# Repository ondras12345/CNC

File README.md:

# CNC
My CNC 1610 configuration and CNC-related notes

See also https://ondra.sluka.cz/projects/1610-cnc/

## Software
- [Grbl firmware](https://github.com/gnea/grbl) (1.1h)
- [Candle Grbl controller](https://github.com/denvi/Candle/) - no longer used
- [bCNC Grbl controller](https://github.com/vlachoudis/bCNC)

## Configuration
- [My Grbl configuration](./GRBL-config.md)
- [My Candle configuration](./Candle)

## Documentation
Links to some useful docs:
- http://linuxcnc.org/docs/html/gcode.html
- https://github.com/Denvi/Candle/wiki
- https://github.com/gnea/grbl/wiki/Grbl-v1.1-Configuration
- https://github.com/gnea/grbl/wiki/Grbl-v1.1-Interface
- https://github.com/gnea/grbl/wiki/Grbl-v1.1-Commands

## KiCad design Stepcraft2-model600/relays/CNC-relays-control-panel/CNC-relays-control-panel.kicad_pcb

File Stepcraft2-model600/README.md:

# Stepcraft2 model 600
This directory contains notes about my Stepcraft CNC machine and accessories:
- Stepcraft 2 - 600 desktop CNC-/3D-System
- HF500 spindle + Hailea ACO-208 air pump ([Stepcraft YouTube](https://www.youtube.com/watch?v=FoeF6cgP0wI))
- Enclosure for desktop CNC/3D systems Stepcraft 600
- UC100 CNC motion controller (currently unused)
- Stepcraft USB module for WinPC-NC (currently unused)
- Stepcraft drag knife
- Stepcraft 3D touch probe
- Stepcraft tool length sensor
- dust shoe

## Spindle
Warning: when controlled with the front panel rotary encoder and button,
the VFD ignores the state of all e-stop switches! As far as I can tell,
this is by design.

## Laser
I wanted to mount the 0.5 W diode laser that I got with my old 1610 CNC
machine in the Stepcraft 43 mm holder, so 3D printed an adapter part:
`laser-mounitng-adapter.FCStd`. The model is parametric, the OD parameter
should probably be increased a bit. See `Params` spreadsheet.
I have also published the model on printables:
https://www.printables.com/model/1005261-stepcraft-43-mm-holder-for-33-mm-laser

## LinuxCNC configuration
### Latency
I am running LinuxCNC with standard preempt_RT kernel on a HP Compaq
dc7700 small form factor (Pentium D). After tuning the BIOS settings
(usual LinuxCNC recommendations + permanently running fans at maximum
speeds), I still had 105 us of base thread latency in `latency-test`.

After settings `i915.enable_dc=0 isolcpus=1` on the linux kernel command
line, I now have 24.5 us worst case latency. (It is important to let
`latency-test` run for a long time, the maximum latency was 14 us
for the first 20 minutes in my case.)

### Stepper drivers
I found this useful webpage: https://www.weigu.lu/other_projects/cnc/grbling_stepcraft/index.html
Apparently, the stepper drivers are A5979.
Based on its datasheet, I set the timings in `stepconf` like this:

| parameter       | value   |
|:---------------:|:-------:|
| Step Time       | 1000 ns |
| Step Space      | 1000 ns |
| Direction Hold  | 200 ns  |
| Direction Setup | 200 ns  |

### Axis config
I got the CNC with a CD that contained a Mach4 configuration file. I used
that as a reference for setting up axes in `stepconf`.

See my [linuxcnc config](../linuxcnc/stepcraft2-model600/).

## Maintenance
- https://cncfaq.us/maintenance/

### 2024-10-26
- The belt situation has gotten worse since the last log, the machine would
  fail to move completely.
- Right (closer to the window) Y pulley was wrapped with steel wire from the
  belt.
- Right Y pulley was moving on the leadscrew - the grub screw was loose.
- Removed right Y pulley from leadscrew. There was grease on the interface,
  I wiped it clean and put the pulley back on.
- Replaced belt.
- Tutorials followed:
  - https://www.youtube.com/watch?v=cZNLv7w0tCs
  - https://www.youtube.com/watch?v=zrz58k_M_2g
  - https://www.youtube.com/watch?v=GKEKqlukmYs
  - https://www.youtube.com/watch?v=RyjEeQAENyk
- When the belt was too loose, it would skip during rapid moves.
- Now it stalls when crashed during rapid, but still skips at F100.
- Now the Y axis is really easy to stall.
- Fixed by tightening the belt a little more. Why does that help?!

### 2024-09-28
- Removed belt cover, it was covered with coarse black dust.
- The side of the belt closer to the work area is damaged and folds over
  easily. This cannot be fixed without replacing the belt.
- Ordered new belt:
  - https://eshop.profitek.cz/stepcraft-cnc-systemy/remen-pro-pohon-v-ose-y/
  - also available from https://shop.stepcraft-systems.com/Tooth-Belt-600

### 2024-09-25
Found issues:
- Right Y axis leadscrew has huge backlash.
- Y belt folds over during Y- jog.

### 2024-09-22
- X axis cable guide was assembled incorrectly by the previous owner, the
  smaller hose was put into the bigger hole in the feedthrough and the bigger
  hose does not fit. Designed a 3D printed part to prevent the wires from
  bending in this location: `X-cable-guide.FCStd`.

### 2024-08
- Cleaned and lubricated all axes.
- Disassembled Z axis (removed stepper) and adjusted roller tension properly.

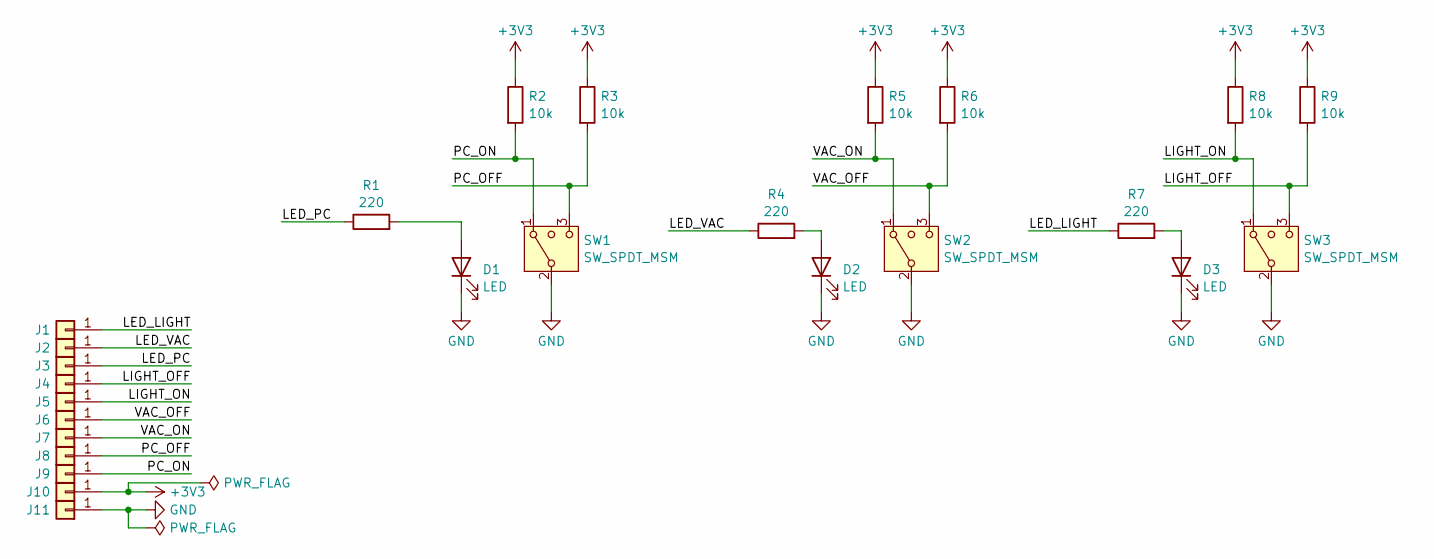
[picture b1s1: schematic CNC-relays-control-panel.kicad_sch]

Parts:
D1, D2, D3: LED; LED_1206_3216Metric_ReverseMount_Hole1.8x2.4mm
J1, J2, J3, J4, J6, J8, J10, J11: Conn_01x01; SolderWire-0.25sqmm_1x01_D0.65mm_OD2mm_Relief
J5, J7, J9: Conn_01x01; SolderWire-0.25sqmm_1x01_D0.65mm_OD2mm_Relief2x
R1, R4, R7: 220; R_1206_3216Metric_Pad1.30x1.75mm_HandSolder
R2, R3, R5, R6, R8, R9: 10k; R_1206_3216Metric_Pad1.30x1.75mm_HandSolder
SW1, SW2, SW3: SW_SPDT_MSM; SPDT_panel_mount

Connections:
+3V3: J10.1, R2.1, R3.1, R5.1, R6.1, R8.1, R9.1
/LED_LIGHT: J1.1, R7.1
/LED_PC: J3.1, R1.1
/LED_VAC: J2.1, R4.1
/LIGHT_OFF: J4.1, R9.2, SW3.3 (4)
/LIGHT_ON: J5.1, R8.2, SW3.1
/PC_OFF: J8.1, R3.2, SW1.3 (4)
/PC_ON: J9.1, R2.2, SW1.1
/VAC_OFF: J6.1, R6.2, SW2.3 (4)
/VAC_ON: J7.1, R5.2, SW2.1
GND: D1.1 (K), D2.1 (K), D3.1 (K), J11.1, SW1.2 (3), SW2.2 (3), SW3.2 (3)
unnamed: D1.2 (A), R1.2
unnamed: D2.2 (A), R4.2
unnamed: D3.2 (A), R7.2

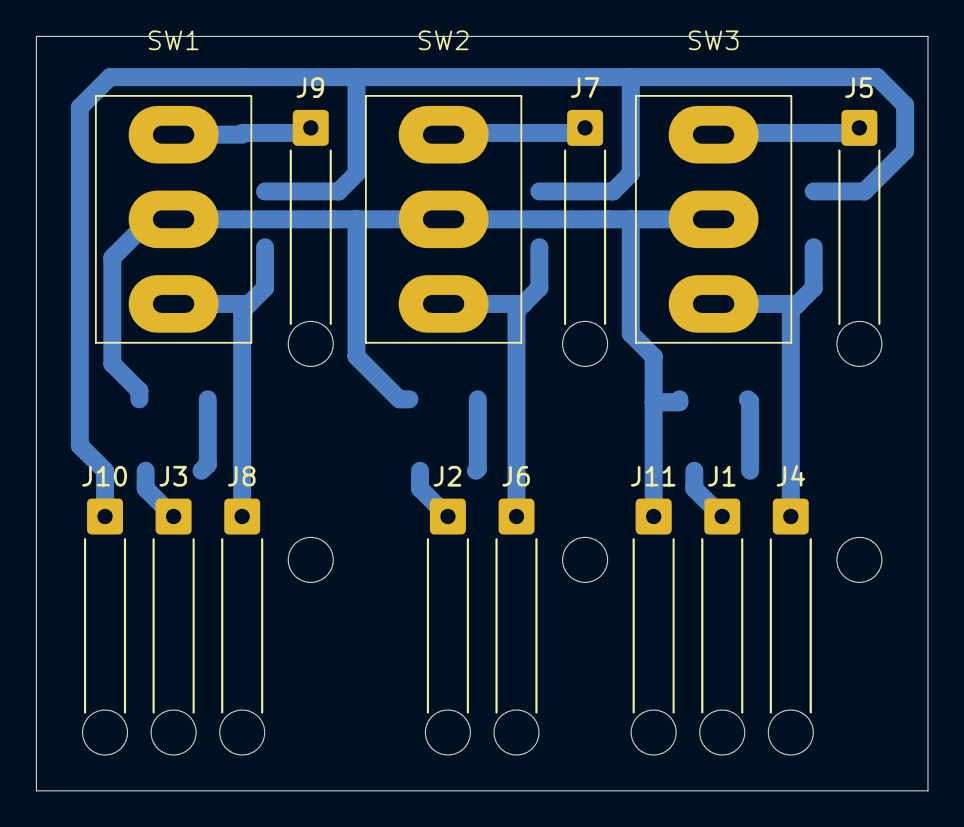
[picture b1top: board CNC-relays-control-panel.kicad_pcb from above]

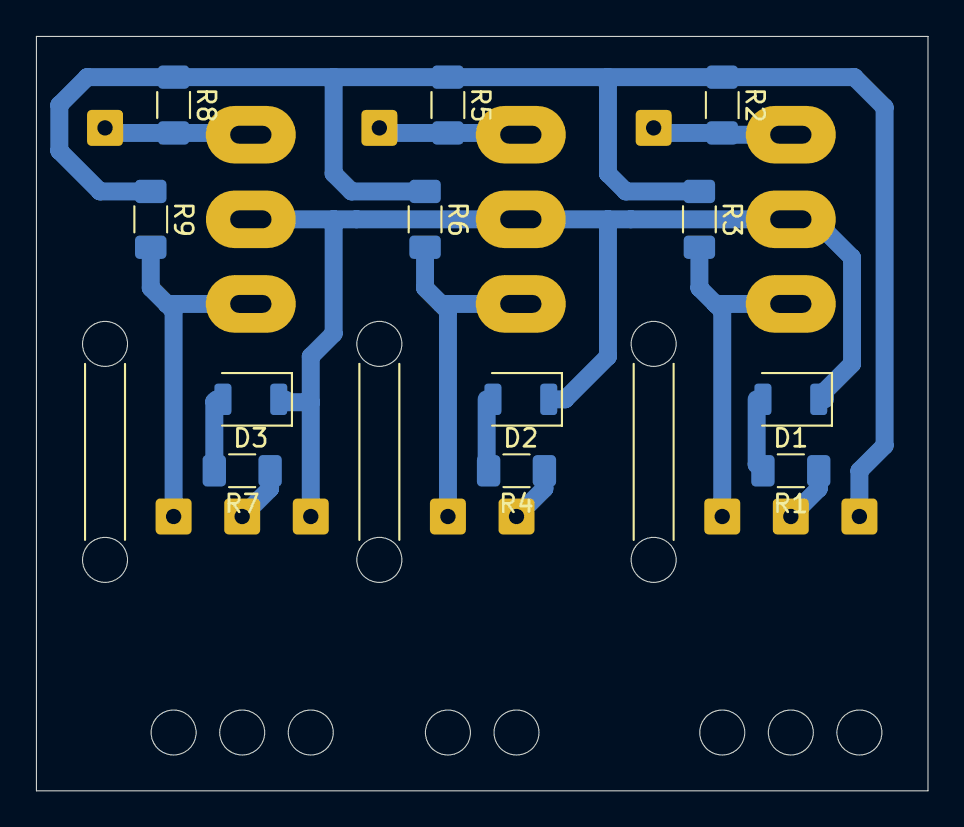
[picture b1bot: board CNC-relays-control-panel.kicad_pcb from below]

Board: 2 copper layers, 49.5 x 41.9 mm, 26 parts (12 on the bottom side), 14 nets.

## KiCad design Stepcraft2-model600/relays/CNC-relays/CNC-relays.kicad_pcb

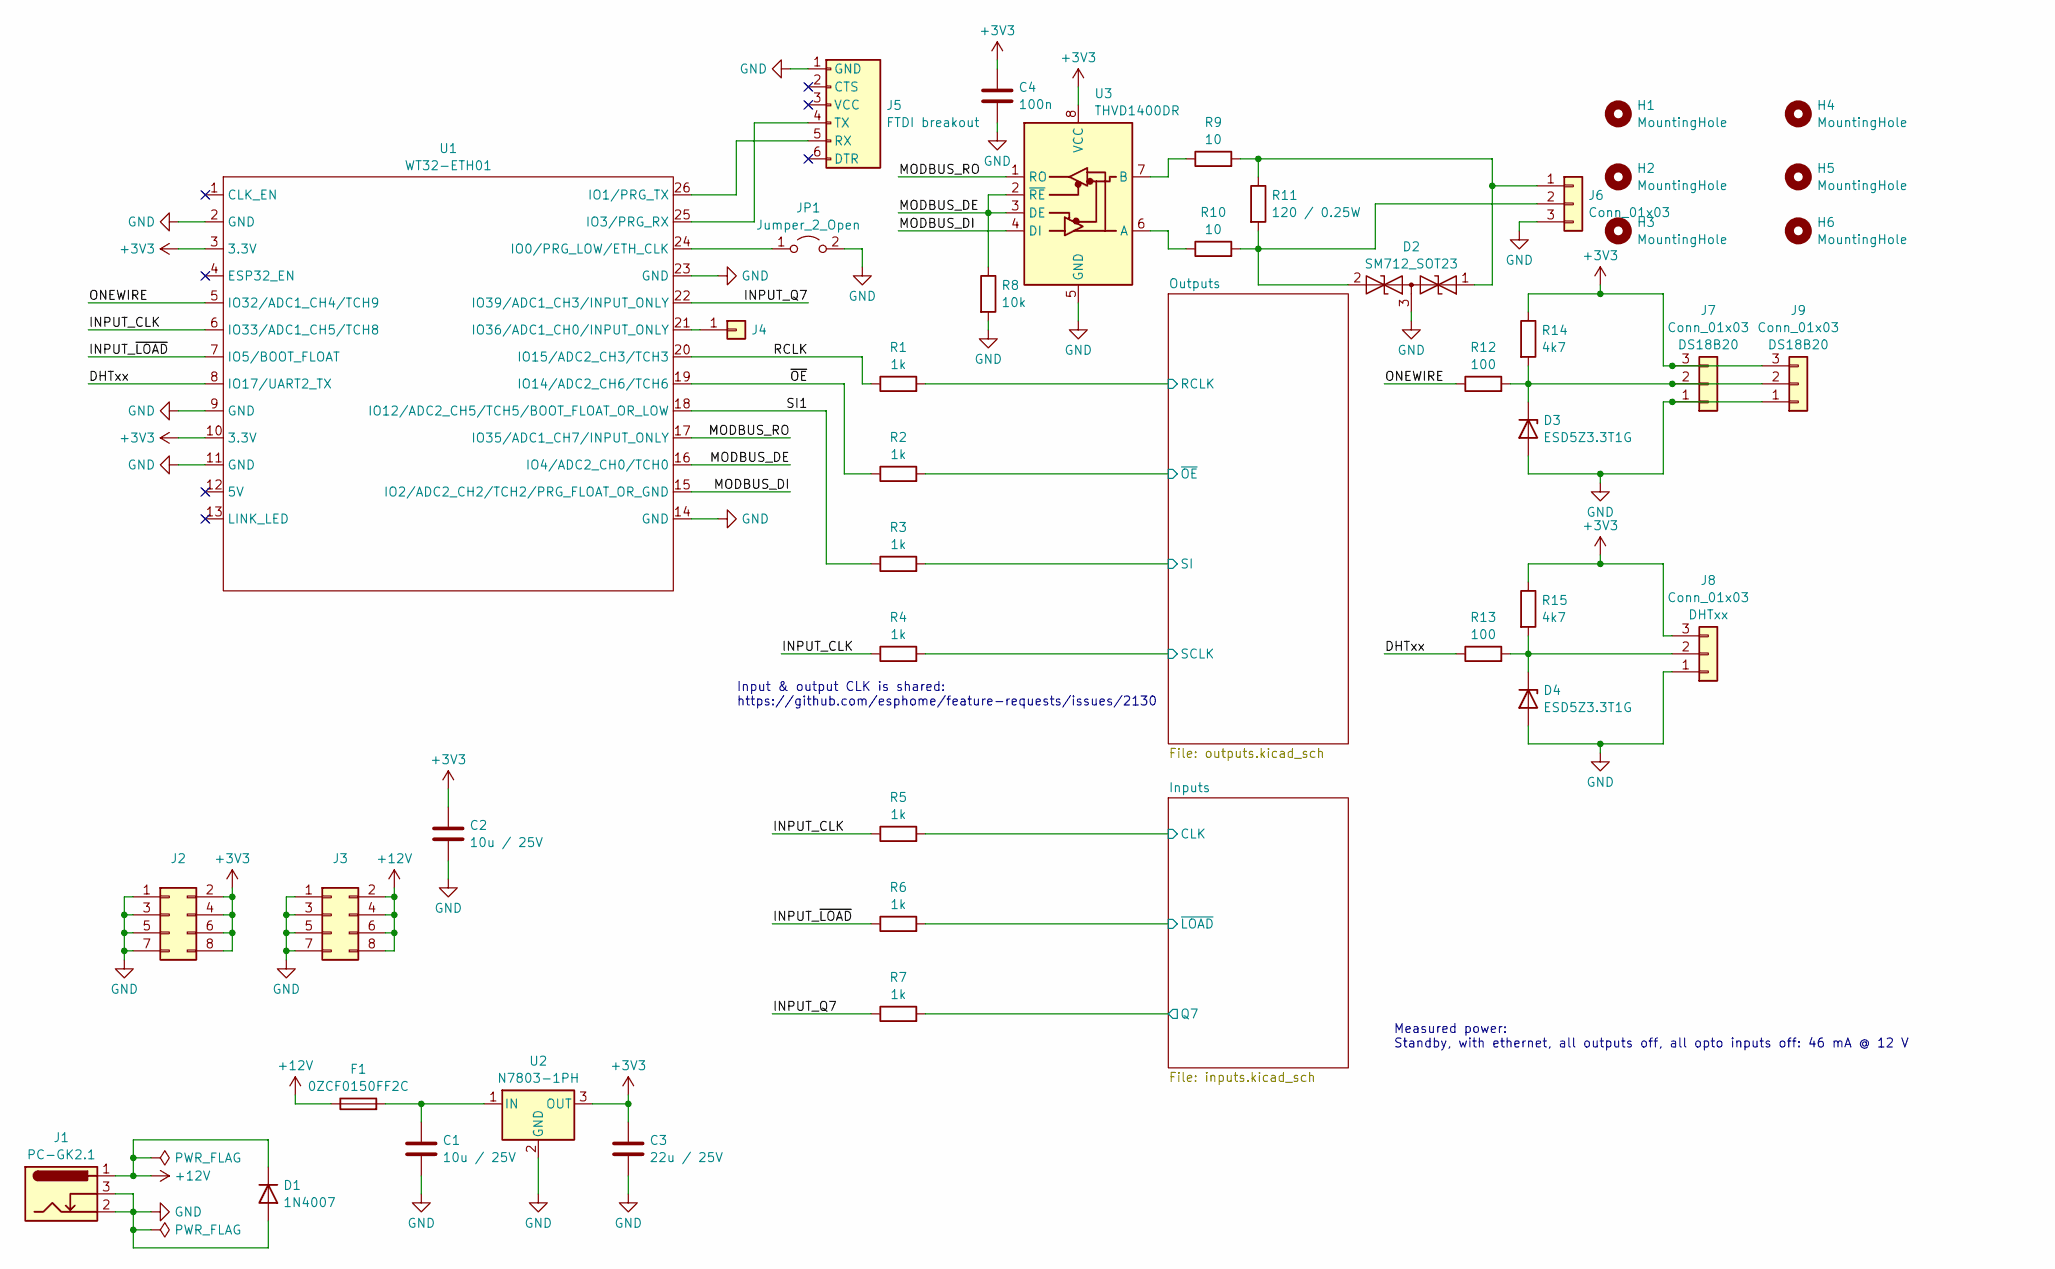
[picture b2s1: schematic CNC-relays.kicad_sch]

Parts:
C1, C2: 10u / 25V; C_1206_3216Metric_Pad1.33x1.80mm_HandSolder
C3: 22u / 25V; C_1206_3216Metric_Pad1.33x1.80mm_HandSolder
C4: 100n; C_1206_3216Metric_Pad1.33x1.80mm_HandSolder
D1: 1N4007; D_SMA_Handsoldering
D2: SM712_SOT23; SOT-23
D3, D4: ESD5Z3.3T1G; D_SOD-523
F1: 0ZCF0150FF2C; Fuse_2920_7451Metric_Pad2.10x5.45mm_HandSolder
H1, H2, H3, H4, H5, H6: MountingHole; MountingHole_3.2mm_M3
J1: PC-GK2.1; BarrelJack_Horizontal
J2, J3: Conn_02x04_Odd_Even; PinHeader_2x04_P2.54mm_Vertical
J4: Conn_01x01; PinHeader_1x01_P2.54mm_Vertical
J5: FTDI breakout; FTDI_breakout
J6, J7, J8, J9: Conn_01x03; Molex_KK-254_AE-6410-03A_1x03_P2.54mm_Vertical
JP1: Jumper_2_Open; PinHeader_1x02_P2.54mm_Vertical
R1, R2, R3, R4, R5, R6, R7: 1k; R_1206_3216Metric_Pad1.30x1.75mm_HandSolder
R8: 10k; R_1206_3216Metric_Pad1.30x1.75mm_HandSolder
R9, R10: 10; R_1206_3216Metric_Pad1.30x1.75mm_HandSolder
R11: 120 / 0.25W; R_1206_3216Metric_Pad1.30x1.75mm_HandSolder
R12, R13: 100; R_1206_3216Metric_Pad1.30x1.75mm_HandSolder
R14, R15: 4k7; R_1206_3216Metric_Pad1.30x1.75mm_HandSolder
U1: WT32-ETH01
U2: N7803-1PH; N78xx-xPH
U3: THVD1400DR; SO-8_3.9x4.9mm_P1.27mm

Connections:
+3V3: C2.1, C3.1, C4.1, J2.2, J2.4, J2.6, J2.8, J7.3, J8.3, J9.3, R14.1, R15.1, U1.3 (3.3V), U1.10 (3.3V), U2.3 (OUT), U3.8 (VCC); also elsewhere on the board
+12V: D1.1 (K), F1.1, J1.1, J3.2, J3.4, J3.6, J3.8; also elsewhere on the board
/DHTxx: R13.1, U1.8 (IO17/UART2_TX)
/INPUT_CLK: R4.1, R5.1, U1.6 (IO33/ADC1_CH5/TCH8)
/INPUT_Q7: R7.1, U1.22 (IO39/ADC1_CH3/INPUT_ONLY)
/INPUT_~LOAD: R6.1, U1.7 (IO5/BOOT_FLOAT)
/Inputs/CLK: R5.2; also elsewhere on the board
/Inputs/Q7: R7.2; also elsewhere on the board
/Inputs/~LOAD: R6.2; also elsewhere on the board
/MODBUS_DE: R8.1, U1.16 (IO4/ADC2_CH0/TCH0), U3.2 (~RE), U3.3 (DE)
/MODBUS_DI: U1.15 (IO2/ADC2_CH2/TCH2/PRG_FLOAT_OR_GND), U3.4 (DI)
/MODBUS_RO: U1.17 (IO35/ADC1_CH7/INPUT_ONLY), U3.1 (RO)
/ONEWIRE: R12.1, U1.5 (IO32/ADC1_CH4/TCH9)
/Outputs/RCLK: R1.2; also elsewhere on the board
/Outputs/SCLK: R4.2; also elsewhere on the board
/Outputs/SI: R3.2; also elsewhere on the board
/Outputs/~OE: R2.2; also elsewhere on the board
/RCLK: R1.1, U1.20 (IO15/ADC2_CH3/TCH3)
/SI1: R3.1, U1.18 (IO12/ADC2_CH5/TCH5/BOOT_FLOAT_OR_LOW)
/~OE: R2.1, U1.19 (IO14/ADC2_CH6/TCH6)
GND: C1.2, C2.2, C3.2, C4.2, D1.2 (A), D2.3 (common), D3.2 (A), D4.2 (A), J1.2, J1.3, J2.1, J2.3, J2.5, J2.7, J3.1, J3.3, J3.5, J3.7, J5.1 (GND), J6.3, J7.1, J8.1, J9.1, JP1.2 (B), R8.2, U1.2 (GND), U1.9 (GND), U1.11 (GND), U1.14 (GND), U1.23 (GND), U2.2 (GND), U3.5 (GND); also elsewhere on the board
unnamed: D2.1 (A1), J6.1, R9.2, R11.1
unnamed: D2.2 (A2), J6.2, R10.2, R11.2
unnamed: D3.1 (K), J7.2, J9.2, R12.2, R14.2
unnamed: D4.1 (K), J8.2, R13.2, R15.2
unnamed: J4.1, U1.21 (IO36/ADC1_CH0/INPUT_ONLY)
unnamed: J5.5 (RX), U1.26 (IO1/PRG_TX)
unnamed: J5.4 (TX), U1.25 (IO3/PRG_RX)
unnamed: JP1.1 (A), U1.24 (IO0/PRG_LOW/ETH_CLK)
unnamed: C1.1, F1.2, U2.1 (IN)
unnamed: R10.1, U3.6 (A)
unnamed: R9.1, U3.7 (B)

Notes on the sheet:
Input & output CLK is shared: https://github.com/esphome/feature-requests/issues/2130
Measured power: Standby, with ethernet, all outputs off, all opto inputs off: 46 mA @ 12 V

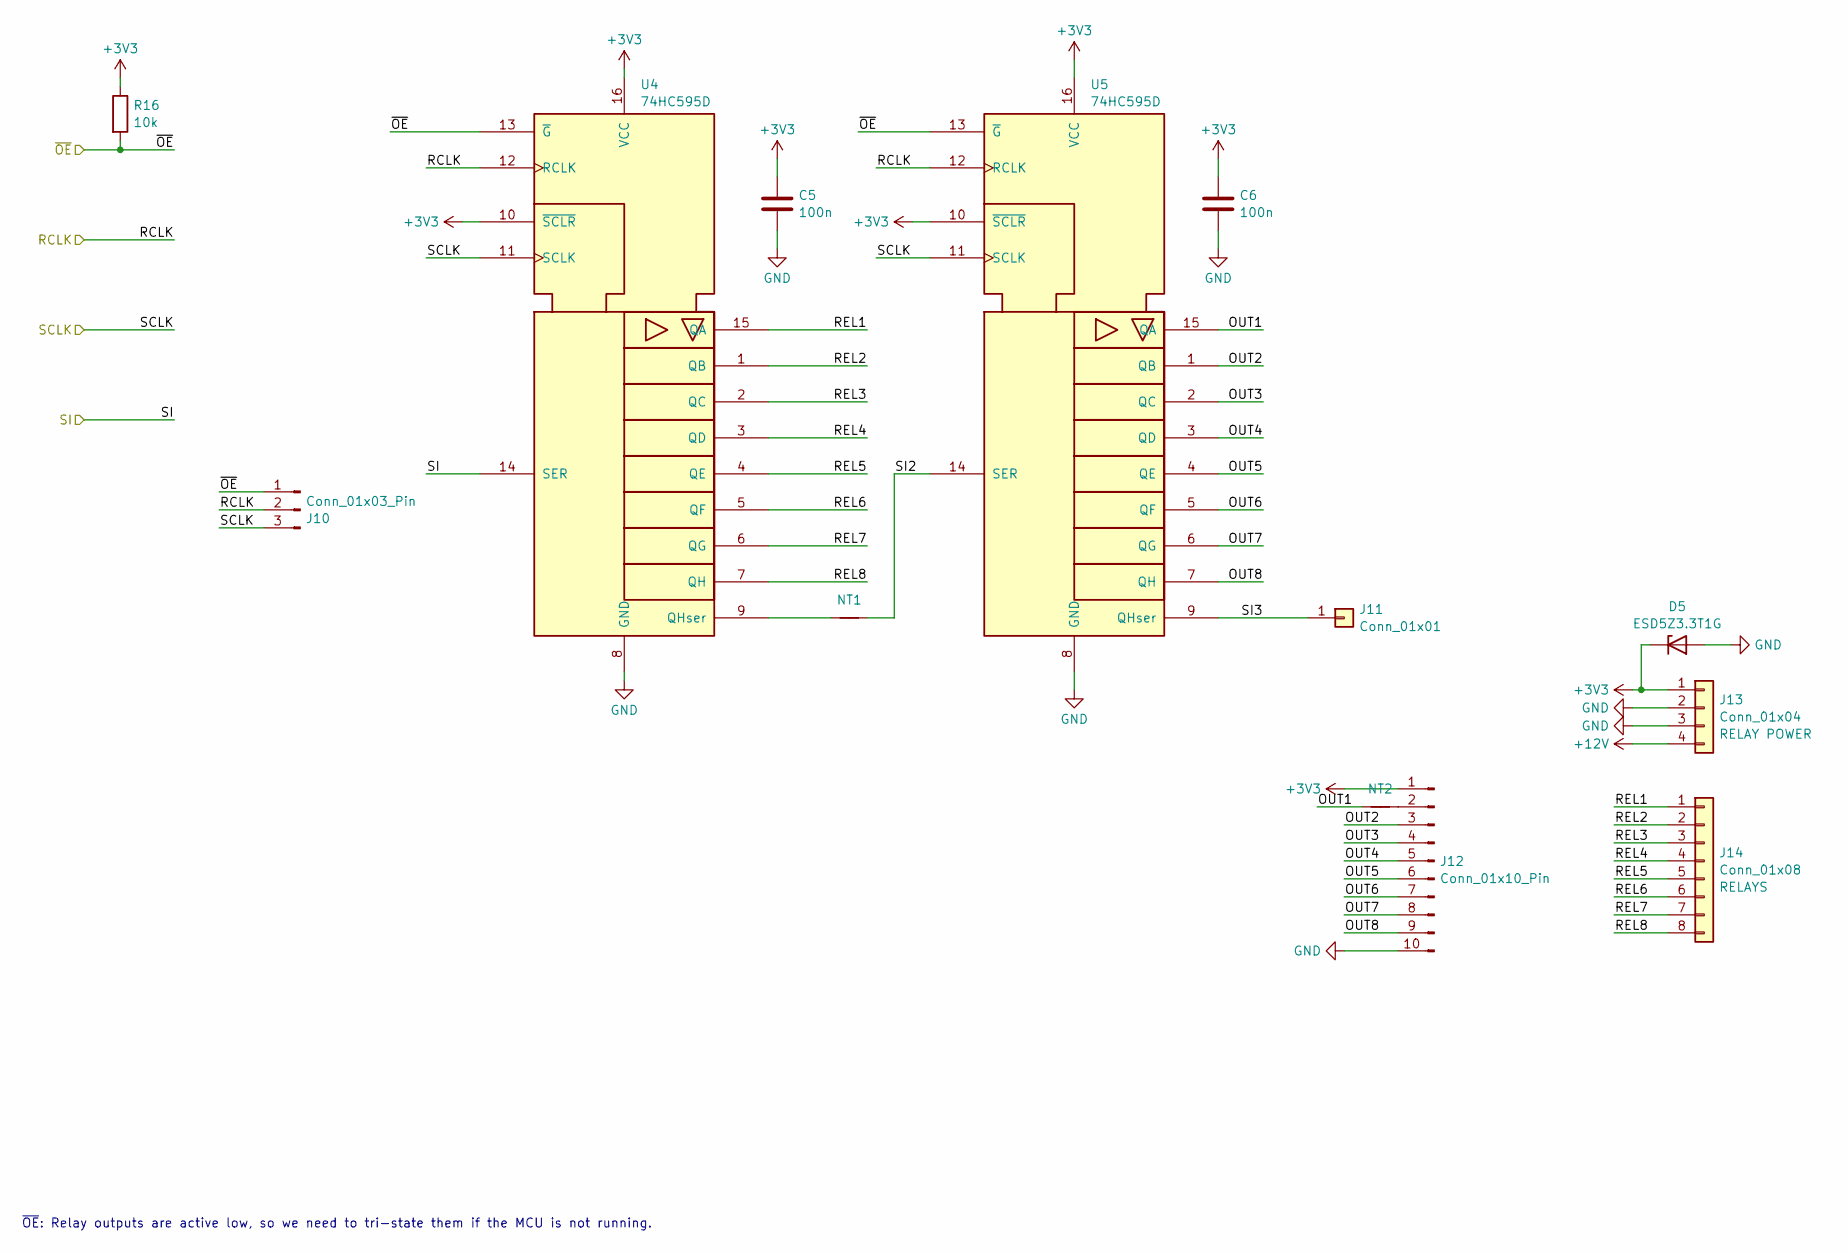
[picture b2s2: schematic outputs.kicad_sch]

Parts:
C5, C6: 100n; C_1206_3216Metric_Pad1.33x1.80mm_HandSolder
D5: ESD5Z3.3T1G; D_SOD-523
J10: Conn_01x03_Pin; PinHeader_1x03_P2.54mm_Vertical
J11: Conn_01x01; PinHeader_1x01_P2.54mm_Vertical
J12: Conn_01x10_Pin; PinHeader_1x10_P2.54mm_Vertical
J13: Conn_01x04; Molex_KK-254_AE-6410-04A_1x04_P2.54mm_Vertical
J14: Conn_01x08; Molex_KK-254_AE-6410-08A_1x08_P2.54mm_Vertical
NT1, NT2: NetTie_2; R_1206_3216Metric_Pad1.30x1.75mm_HandSolder
R16: 10k; R_1206_3216Metric_Pad1.30x1.75mm_HandSolder
U4, U5: 74HC595D; SO-16_3.9x9.9mm_P1.27mm

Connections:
+3V3: C5.1, C6.1, D5.1 (K), J12.1, J13.1, R16.1, U4.10 (~SCLR), U4.16 (VCC), U5.10 (~SCLR), U5.16 (VCC); also elsewhere on the board
+12V: J13.4; also elsewhere on the board
/Outputs/OUT1: NT2.1, U5.15 (QA)
/Outputs/OUT2: J12.3, U5.1 (QB)
/Outputs/OUT3: J12.4, U5.2 (QC)
/Outputs/OUT4: J12.5, U5.3 (QD)
/Outputs/OUT5: J12.6, U5.4 (QE)
/Outputs/OUT6: J12.7, U5.5 (QF)
/Outputs/OUT7: J12.8, U5.6 (QG)
/Outputs/OUT8: J12.9, U5.7 (QH)
/Outputs/RCLK: J10.2, U4.12 (RCLK), U5.12 (RCLK); also elsewhere on the board
/Outputs/REL1: J14.1, U4.15 (QA)
/Outputs/REL2: J14.2, U4.1 (QB)
/Outputs/REL3: J14.3, U4.2 (QC)
/Outputs/REL4: J14.4, U4.3 (QD)
/Outputs/REL5: J14.5, U4.4 (QE)
/Outputs/REL6: J14.6, U4.5 (QF)
/Outputs/REL7: J14.7, U4.6 (QG)
/Outputs/REL8: J14.8, U4.7 (QH)
/Outputs/SCLK: J10.3, U4.11 (SCLK), U5.11 (SCLK); also elsewhere on the board
/Outputs/SI: U4.14 (SER); also elsewhere on the board
/Outputs/SI2: NT1.2, U5.14 (SER)
/Outputs/SI3: J11.1, U5.9 (QHser)
/Outputs/~OE: J10.1, R16.2, U4.13 (~G), U5.13 (~G); also elsewhere on the board
GND: C5.2, C6.2, D5.2 (A), J12.10, J13.2, J13.3, U4.8 (GND), U5.8 (GND); also elsewhere on the board
unnamed: J12.2, NT2.2
unnamed: NT1.1, U4.9 (QHser)

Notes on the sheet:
~{OE}: Relay outputs are active low, so we need to tri-state them if the MCU is not running.

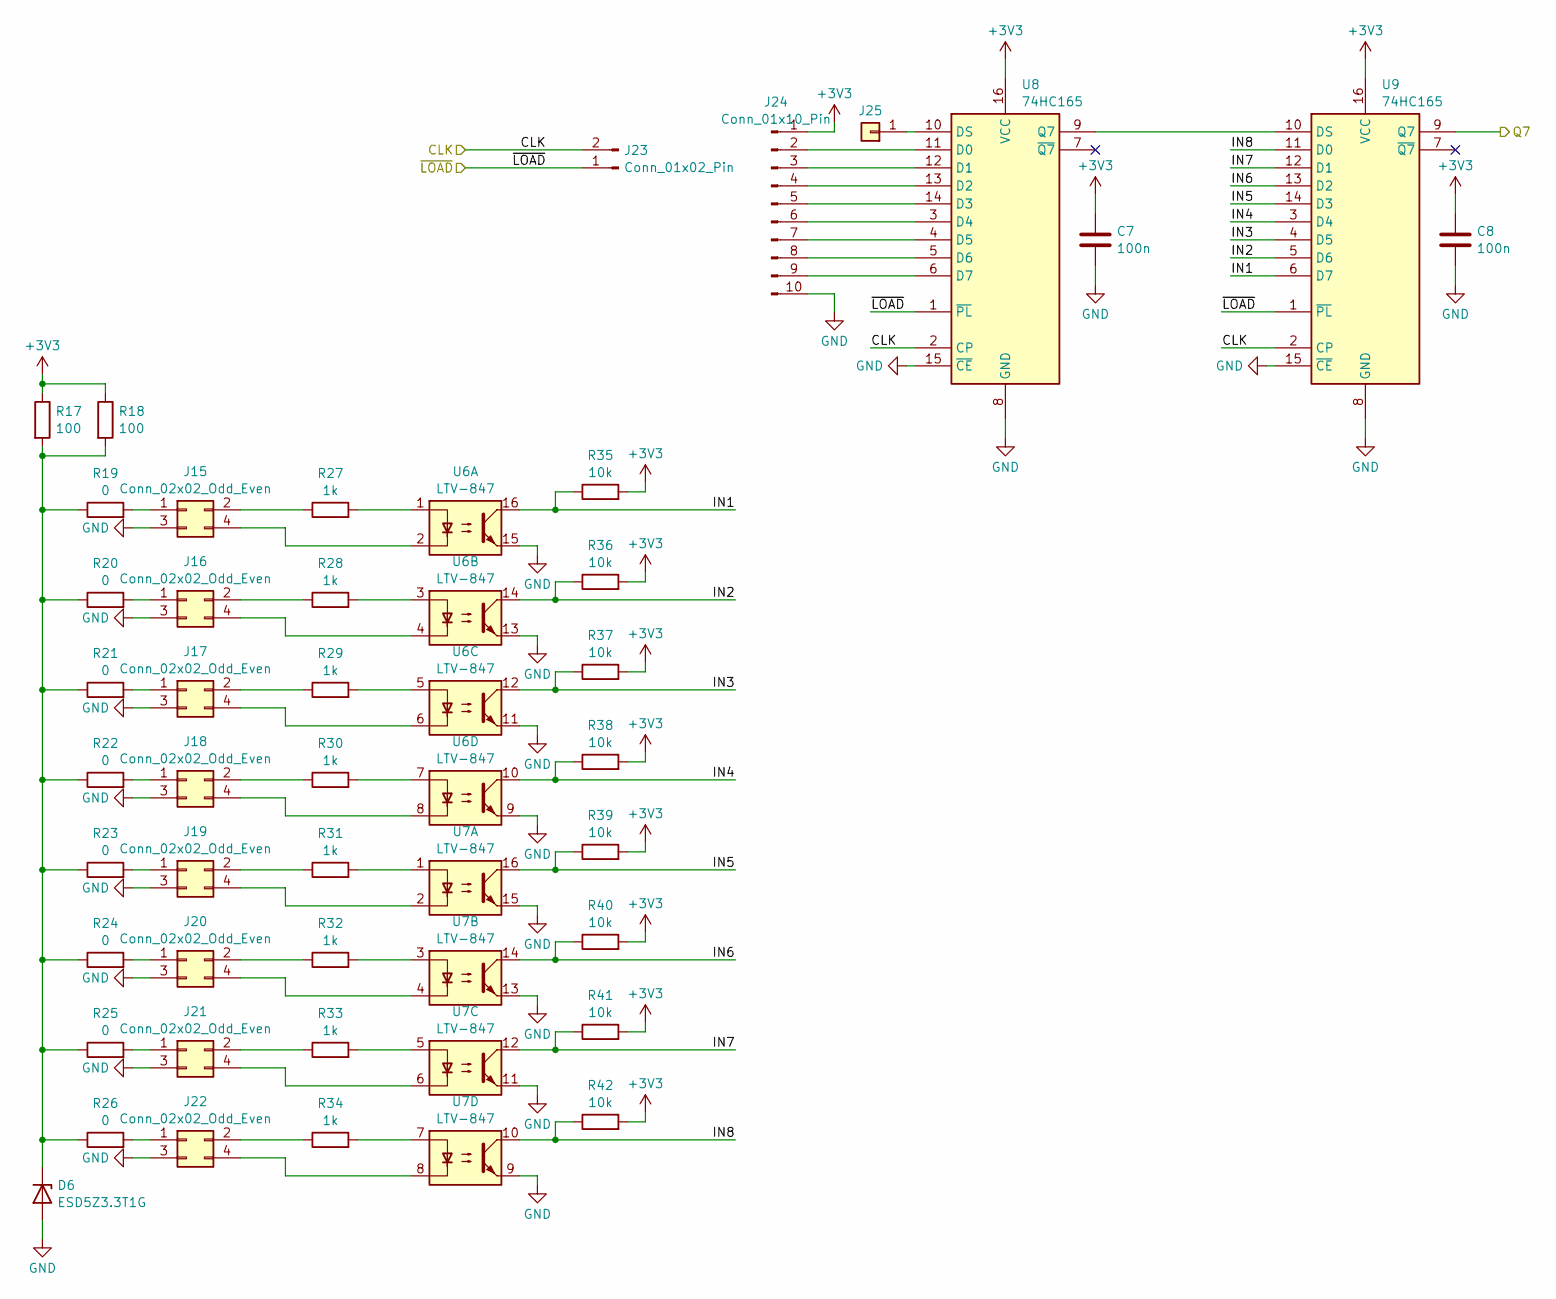
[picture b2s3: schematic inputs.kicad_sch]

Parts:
C7, C8: 100n; C_1206_3216Metric_Pad1.33x1.80mm_HandSolder
D6: ESD5Z3.3T1G; D_SOD-523
J15, J16, J17, J18, J19, J20, J21, J22: Conn_02x02_Odd_Even; PinHeader_2x02_P2.54mm_Vertical
J23: Conn_01x02_Pin; PinHeader_1x02_P2.54mm_Vertical
J24: Conn_01x10_Pin; PinHeader_1x10_P2.54mm_Vertical
J25: Conn_01x01; PinHeader_1x01_P2.54mm_Vertical
R17, R18: 100; R_1206_3216Metric_Pad1.30x1.75mm_HandSolder
R19, R20, R21, R22, R23, R24, R25, R26: 0; R_1206_3216Metric_Pad1.30x1.75mm_HandSolder
R27, R28, R29, R30, R31, R32, R33, R34: 1k; R_1206_3216Metric_Pad1.30x1.75mm_HandSolder
R35, R36, R37, R38, R39, R40, R41, R42: 10k; R_1206_3216Metric_Pad1.30x1.75mm_HandSolder
U6, U7: LTV-847; DIP-16_W7.62mm
U8, U9: 74HC165; SO-16_3.9x9.9mm_P1.27mm

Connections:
+3V3: C7.1, C8.1, J24.1, R17.1, R18.1, R35.2, R36.2, R37.2, R38.2, R39.2, R40.2, R41.2, R42.2, U8.16 (VCC), U9.16 (VCC); also elsewhere on the board
/Inputs/CLK: J23.2, U8.2 (CP), U9.2 (CP); also elsewhere on the board
/Inputs/IN1: R35.1, U6.16, U9.6 (D7)
/Inputs/IN2: R36.1, U6.14, U9.5 (D6)
/Inputs/IN3: R37.1, U6.12, U9.4 (D5)
/Inputs/IN4: R38.1, U6.10, U9.3 (D4)
/Inputs/IN5: R39.1, U7.16, U9.14 (D3)
/Inputs/IN6: R40.1, U7.14, U9.13 (D2)
/Inputs/IN7: R41.1, U7.12, U9.12 (D1)
/Inputs/IN8: R42.1, U7.10, U9.11 (D0)
/Inputs/Q7: U9.9 (Q7); also elsewhere on the board
/Inputs/~LOAD: J23.1, U8.1 (~PL), U9.1 (~PL); also elsewhere on the board
GND: C7.2, C8.2, D6.2 (A), J15.3, J16.3, J17.3, J18.3, J19.3, J20.3, J21.3, J22.3, J24.10, U6.9, U6.11, U6.13, U6.15, U7.9, U7.11, U7.13, U7.15, U8.8 (GND), U8.15 (~CE), U9.8 (GND), U9.15 (~CE); also elsewhere on the board
unnamed: D6.1 (K), R17.2, R18.2, R19.1, R20.1, R21.1, R22.1, R23.1, R24.1, R25.1, R26.1
unnamed: J15.1, R19.2
unnamed: J15.2, R27.1
unnamed: J15.4, U6.2
unnamed: J16.1, R20.2
unnamed: J16.2, R28.1
unnamed: J16.4, U6.4
unnamed: J17.1, R21.2
unnamed: J17.2, R29.1
unnamed: J17.4, U6.6
unnamed: J18.1, R22.2
unnamed: J18.2, R30.1
unnamed: J18.4, U6.8
unnamed: J19.1, R23.2
unnamed: J19.2, R31.1
unnamed: J19.4, U7.2
unnamed: J20.1, R24.2
unnamed: J20.2, R32.1
unnamed: J20.4, U7.4
unnamed: J21.1, R25.2
unnamed: J21.2, R33.1
unnamed: J21.4, U7.6
unnamed: J22.1, R26.2
unnamed: J22.2, R34.1
unnamed: J22.4, U7.8
unnamed: J24.2, U8.11 (D0)
unnamed: J24.3, U8.12 (D1)
unnamed: J24.4, U8.13 (D2)
unnamed: J24.5, U8.14 (D3)
unnamed: J24.6, U8.3 (D4)
unnamed: J24.7, U8.4 (D5)
unnamed: J24.8, U8.5 (D6)
unnamed: J24.9, U8.6 (D7)
unnamed: J25.1, U8.10 (DS)
unnamed: R27.2, U6.1
unnamed: R28.2, U6.3
unnamed: R29.2, U6.5
unnamed: R30.2, U6.7
unnamed: R31.2, U7.1
unnamed: R32.2, U7.3
unnamed: R33.2, U7.5
unnamed: R34.2, U7.7
unnamed: U8.9 (Q7), U9.10 (DS)

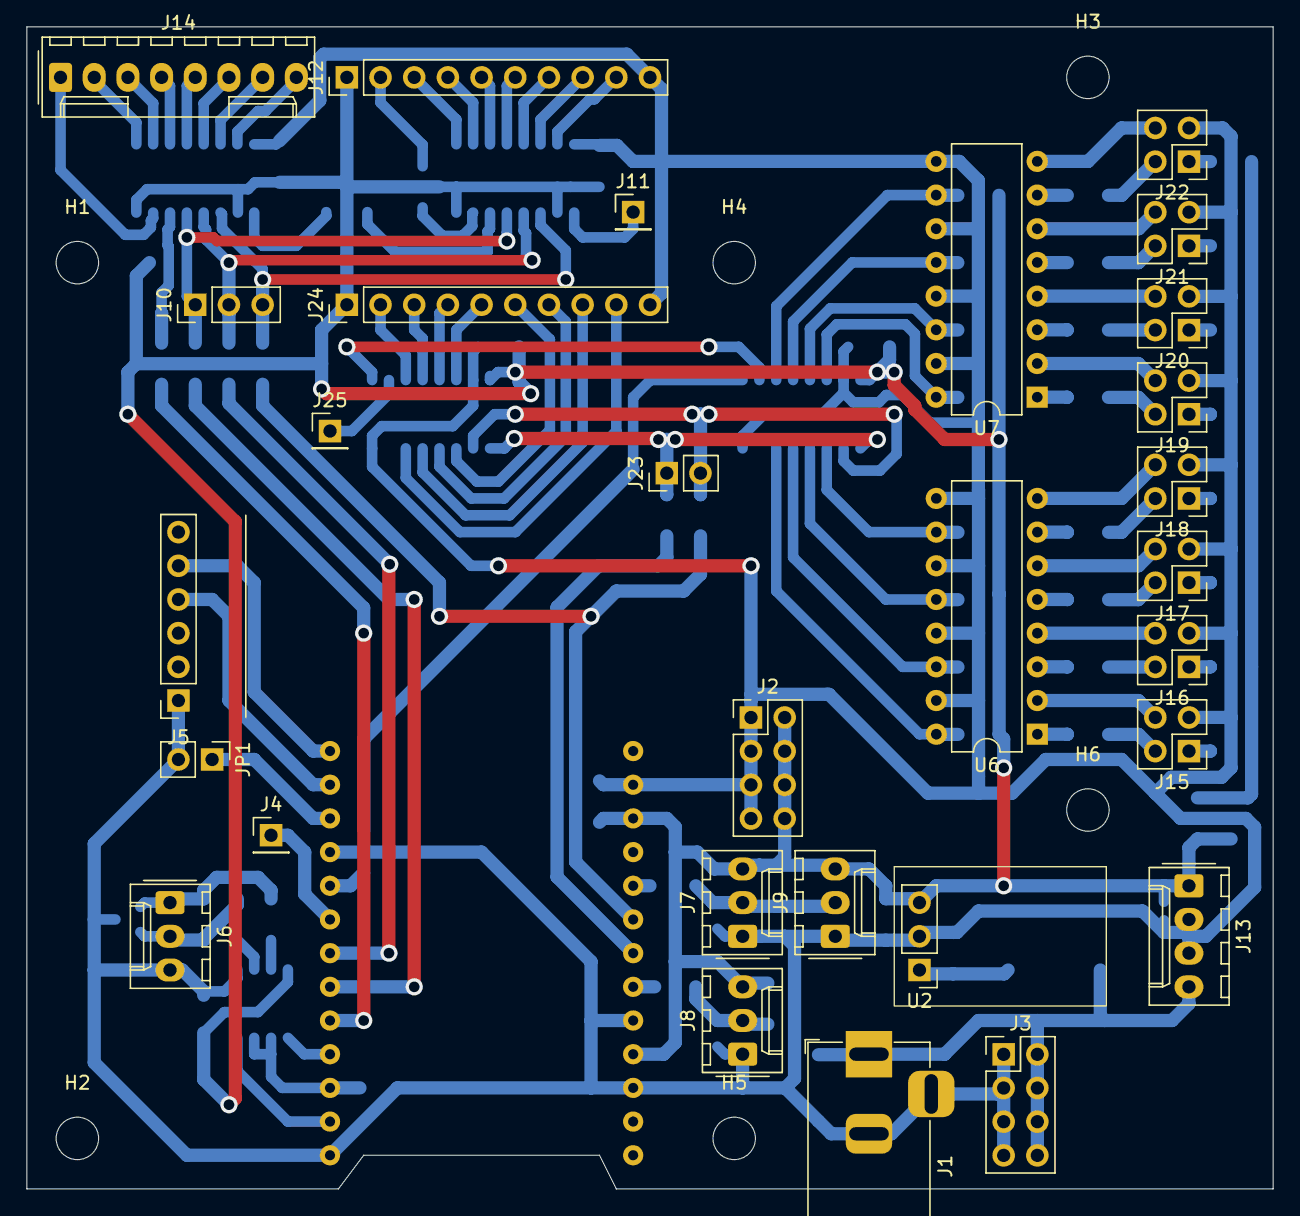
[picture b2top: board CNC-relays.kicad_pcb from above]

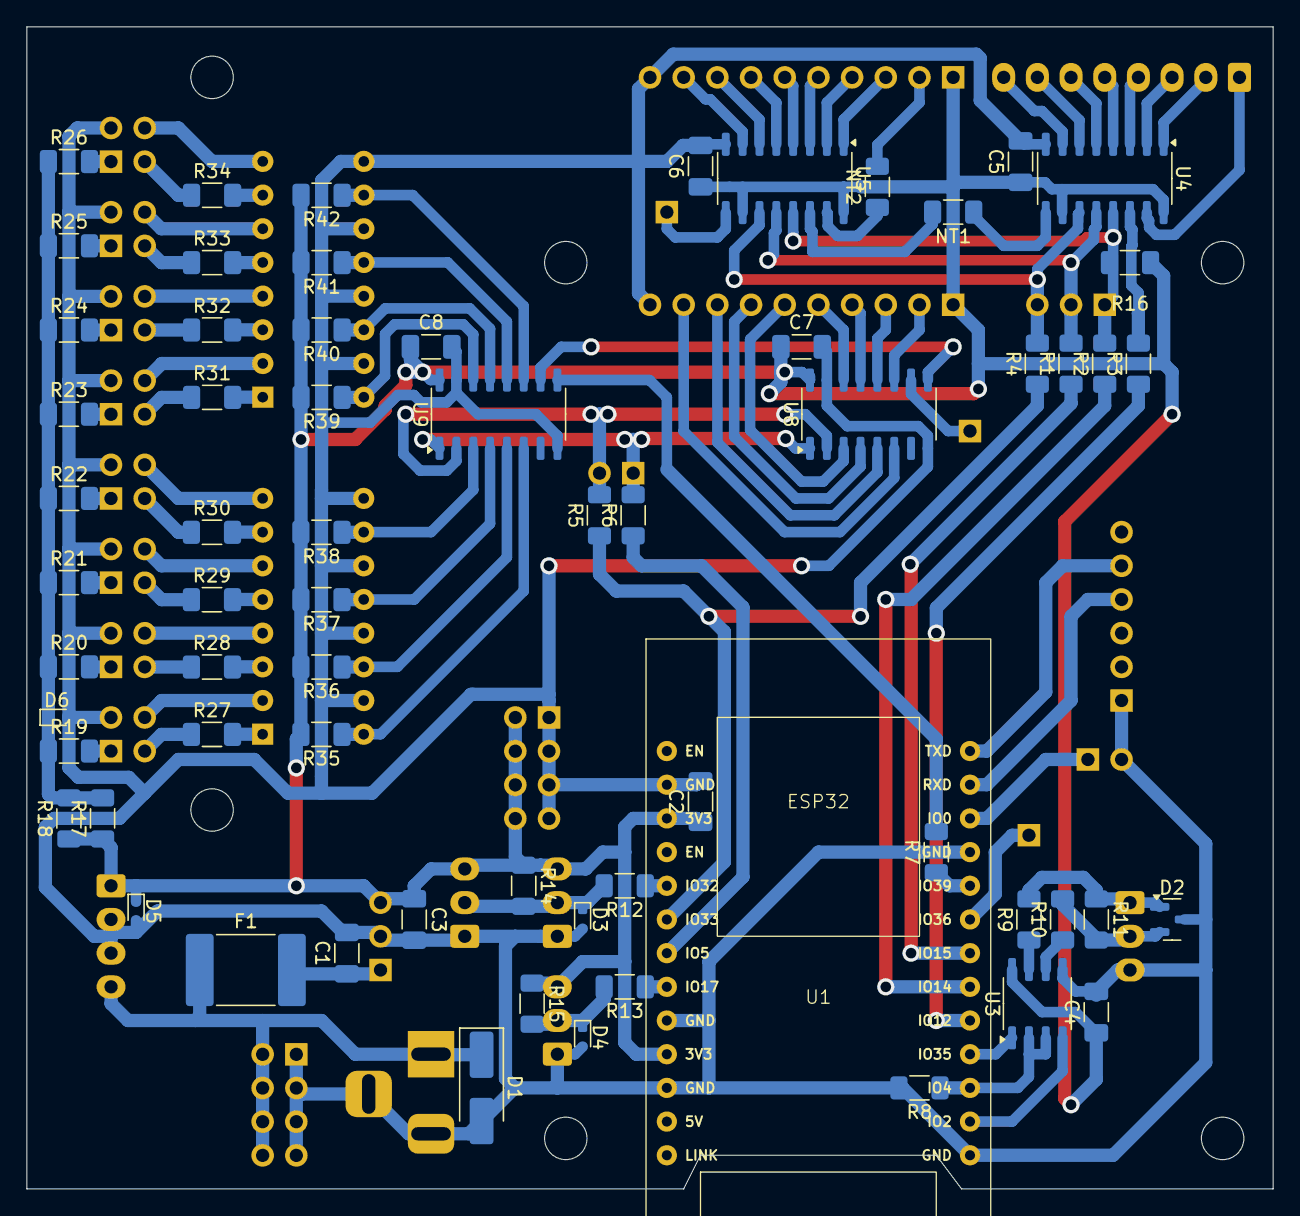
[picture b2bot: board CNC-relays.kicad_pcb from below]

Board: 2 copper layers, 94.0 x 87.6 mm, 100 parts (65 on the bottom side), 103 nets.

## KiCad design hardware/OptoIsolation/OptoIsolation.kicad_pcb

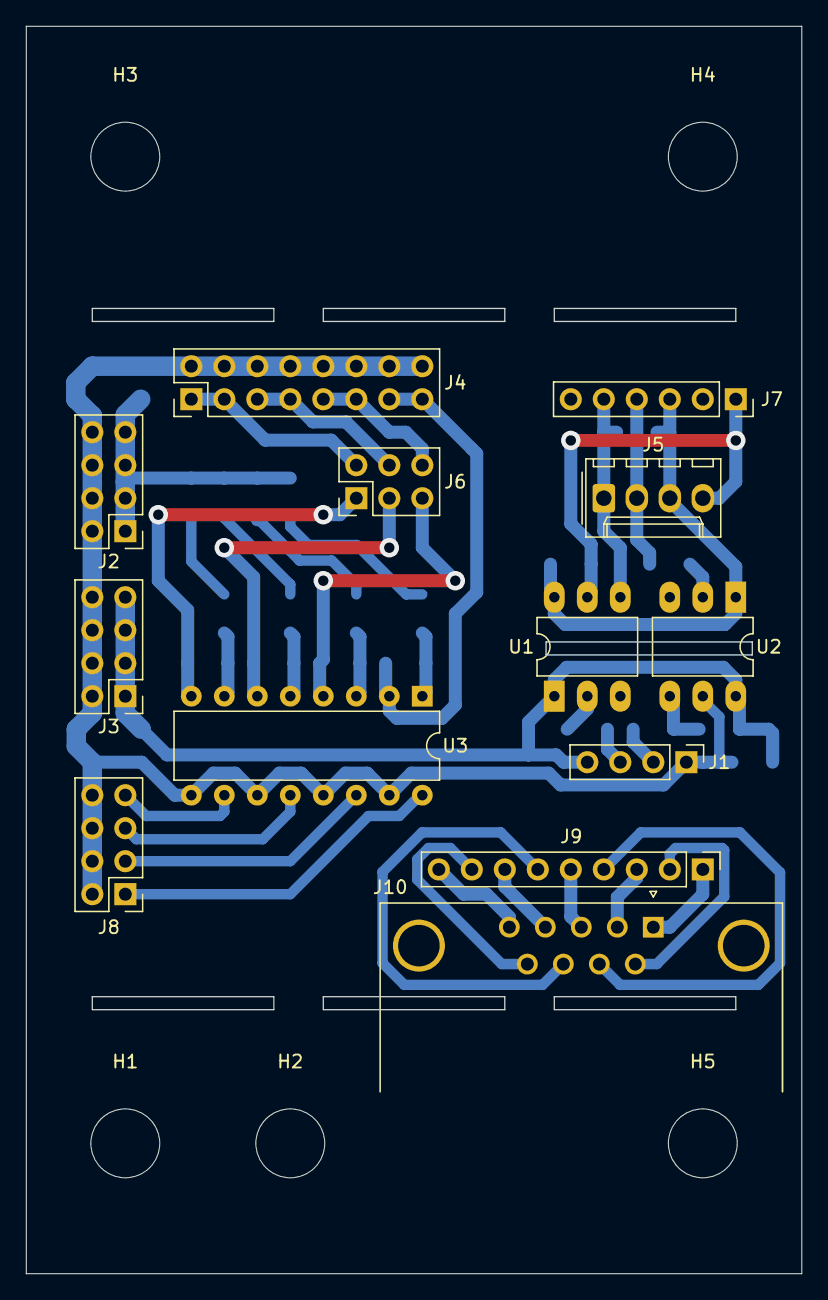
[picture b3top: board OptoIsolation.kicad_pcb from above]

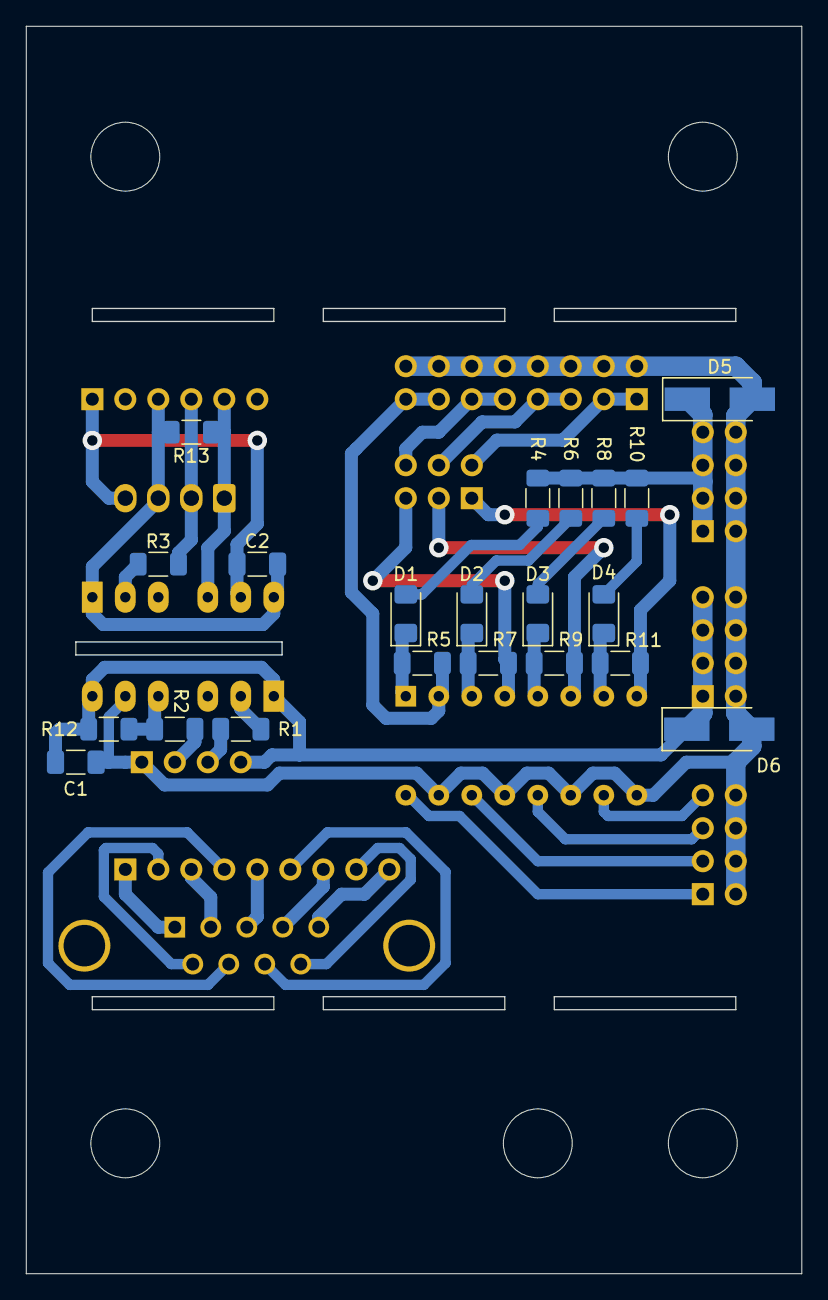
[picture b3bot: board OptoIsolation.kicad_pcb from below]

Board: 2 copper layers, 59.6 x 96.0 mm, 39 parts (21 on the bottom side), 40 nets.

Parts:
C1, C2: 100n; C_1206_3216Metric_Pad1.33x1.80mm_HandSolder
D1, D2, D3, D4: LED; LED_1206_3216Metric_Pad1.42x1.75mm_HandSolder
D5, D6: 1N4007; D_SMA_Handsoldering
H1, H2, H3, H4, H5: MountingHole; MountingHole_5.3mm_M5
J1: UART CNC; PinHeader_1x04_P2.54mm_Vertical
J2: POWER 12V; PinHeader_2x04_P2.54mm_Vertical
J3: POWER 5V; PinHeader_2x04_P2.54mm_Vertical
J4: Conn_02x08_Odd_Even; PinHeader_2x08_P2.54mm_Vertical
J5: UART PC; Molex_KK-254_AE-6410-04A_1x04_P2.54mm_Vertical
J6: Conn_02x03_Odd_Even; PinHeader_2x03_P2.54mm_Vertical
J7: UART FTDI BREAKOUT; PinSocket_1x06_P2.54mm_Vertical
J8: OUT TO WOODPECKER PCB; PinHeader_2x04_P2.54mm_Vertical
J9: CONTROL PANEL BREAKOUT; PinHeader_1x09_P2.54mm_Vertical
J10: CONTROL PANEL; DSUB-9_Female_Horizontal_P2.77x2.84mm_EdgePinOffset9.90mm_H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
R1, R2, R3, R4, R6, R8, R10, R12, R13: 1k; R_1206_3216Metric_Pad1.30x1.75mm_HandSolder
R5, R7, R9, R11: 330; R_1206_3216Metric_Pad1.30x1.75mm_HandSolder
U1, U2: H11L1; DIP-6_W7.62mm_LongPads
U3: LTV-847; DIP-16_W7.62mm

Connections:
+5V: C1.1, D6.1, J1.4, J3.1, J3.3, J3.5, J3.7, R12.2, U1.1, U2.6
+12V: D5.1, J2.1, J2.3, J2.5, J2.7, R4.1, R6.1, R8.1, R10.1
/5V_PC: C2.1, J5.3, J7.3, R13.2, U1.6, U2.1
/END_X_IN: J4.1, J4.3, J6.2
/END_X_OUT: J8.7, U3.10
/END_Y_IN: J4.5, J4.7, J6.4
/END_Y_OUT: J8.5, U3.12
/END_Z_IN: J4.9, J4.11, J6.6
/END_Z_OUT: J8.3, U3.14
/GND_PC: C2.2, J5.4, J7.1, U1.5
/PROBE_IN: J4.13, J4.15, R5.2, U3.2
/PROBE_OUT: J8.1, U3.16
/RX_CNC: J1.2, R2.2
/RX_PC: J5.1, J7.5, R13.1, U1.4
/TX_CNC: J1.3, R1.2
/TX_PC: J5.2, J7.4, R3.2
GND: C1.2, D5.2, D6.2, J1.1, J2.2, J2.4, J2.6, J2.8, J3.2, J3.4, J3.6, J3.8, J4.2, J4.4, J4.6, J4.8, J4.10, J4.12, J4.14, J4.16, J8.2, J8.4, J8.6, J8.8, U2.5, U3.9, U3.11, U3.13, U3.15
unnamed: D1.1, R5.1, U3.1
unnamed: D1.2, R4.2
unnamed: D2.1, R7.1, U3.3
unnamed: D2.2, R6.2
unnamed: D3.1, R9.1, U3.5
unnamed: D3.2, R8.2
unnamed: D4.1, R11.1, U3.7
unnamed: D4.2, R10.2
unnamed: J6.1, R11.2, U3.8
unnamed: J6.3, R9.2, U3.6
unnamed: J6.5, R7.2, U3.4
unnamed: J9.1, J10.1
unnamed: J9.3, J10.2
unnamed: J9.5, J10.3
unnamed: J9.7, J10.4
unnamed: J9.9, J10.5
unnamed: J9.2, J10.6
unnamed: J9.4, J10.7
unnamed: J9.6, J10.8
unnamed: J9.8, J10.9
unnamed: R1.1, U1.2
unnamed: R3.1, U2.2
unnamed: R2.1, R12.1, U2.4
